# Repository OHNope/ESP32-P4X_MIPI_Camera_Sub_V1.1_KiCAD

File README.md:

# ESP32-P4-Function-EV-Board MIPI Camera Sub V1.1 — KiCad

[中文](#中文) | [English](#english)

---

## 中文

这是 Espressif 官方开发板 **ESP32-P4-Function-EV-Board** 的 MIPI 相机转接板（Camera Adapter Board, Camera Sub V1.1, 2024-05-29）的 KiCad 工程。设计版权归 Espressif 所有；本仓库只是把官方 OrCAD/Allegro 设计数据转成 KiCad，并修复了导入过程中出现的问题。

### 官方资料

- 开发板用户指南 (v1.5.2)：<https://docs.espressif.com/projects/esp-dev-kits/en/latest/esp32p4/esp32-p4-function-ev-board/user_guide.html>
- 相机转接板原理图 (PDF)：<https://dl.espressif.com/dl/schematics/esp32-p4-function-ev-board-camera-subboard-schematics.pdf>
- 相机转接板 PCB 布局 (PDF)：<https://dl.espressif.com/dl/schematics/esp32-p4-function-ev-board-camera-subboard-pcb-layout.pdf>
- 官方参考设计包（OrCAD DSN、Allegro BRD、Gerber、BOM、贴片文件）：<https://dl.espressif.com/schematics/CameraAdapterBoardReferenceDesign.zip>

### 为什么需要这个仓库

KiCad 的 OrCAD `.DSN` 导入功能目前只在 Nightly (10.99) 里有，正式版要等到 KiCad 11。即使能导入，解析结果和 Board Setup 的映射也有不少问题，导入后直接跑会有大量 ERC/DRC 报错。本工程逐项修正了这些导入问题，电路连接与官方设计保持一致。

### 打开方式

- **KiCad 10.0 及以上**即可打开（已在 KiCad 10.0.5 正式版和 Nightly 10.99 上验证）。转换和修复是在 Nightly 10.99 里完成的，之后用 KiCad 10.0.5 原生重存为 10.0 格式，以便正式版直接使用，KiCad 11 也能打开。降级前后的网表、焊盘/过孔坐标、坐标文件、Gerber 与钻孔几何、ERC/DRC 结果逐项比对一致。
- 用 KiCad 打开 `SCH_ESP32-P4_FUNCTION_EV_BOARD_MIPI_Camera_Sub_V1.1_20240529.kicad_pro`。
- 符号库 `orcad_import` 和封装库 `Camera_Sub` 都在工程目录内，已通过项目库表 (`sym-lib-table` / `fp-lib-table`) 注册，不依赖任何全局库。

### 检查结果（KiCad 10.0.5 与 Nightly 10.99 `kicad-cli`，结果相同）

| 检查 | 结果 |
| --- | --- |
| ERC | 0 |
| DRC 错误 | 0 |
| 未连接项 | 0 |
| 原理图 / PCB 一致性 | 0 |
| DRC 警告 | 57 条丝印警告，与官方 Gerber 一致（见下文） |

剩余 57 条丝印警告来自原设计本身，已对照官方 Gerber 确认，没有修改：位号字高 0.635 mm 低于 KiCad 默认下限 0.8 mm（33 条）；J1/SW1 的丝印跨过焊盘，生产时由阻焊裁掉（23 条）；"Same-Side FFC" 文字与 R20 丝印相碰（1 条）。

### 修复内容

原理图（OrCAD 导入）：
- 导入器把 OrCAD 的 "Power" 引脚全部映射为 `power_in`，导致 LDO（U1/U2）的 OUT 也成了电源输入，1V8/2V8 无驱动源。已改为 `power_out`。
- 符号库 `orcad_import` 未注册：导出为项目库 `orcad_import.kicad_sym`。
- `Footprint` 字段为空（封装名在 `OrCAD Footprint` 字段中）：已填写为 `Camera_Sub:<封装名>`。
- 3V3/GND 由 J1 从主板引入，添加 PWR_FLAG。
- 4 根 OrCAD 风格的带标签短线一端悬空：截短到标签位置，拓扑不变。
- 工程把原理图图框设为 `empty.kicad_wks`（只画 OrCAD 自带的图框和标题栏），但没有这个文件：KiCad 会退回默认图框，与 OrCAD 标题栏重叠，KiBot 打印原理图时直接报错。已补上空图框文件。

PCB（Allegro 导入）：
- 封装没有库名、Value 和原理图关联：从板上实物封装生成项目封装库 `Camera_Sub.pretty`，补全库名、Value、符号关联和原理图字段。
- 网络名与原理图不一致：标签网络加 `/` 前缀；`Net_xx` 单焊盘网络改为原理图的 `unconnected-(…)` 名称。已逐焊盘与原理图网表核对。
- 两个无位号的 Allegro 机械图形：命名为 MECH1/MECH2 并设为 board-only。
- 约束为 KiCad 默认值：恢复 Allegro 约束（最小线宽 0.127 mm、最小钻孔 0.25 mm）。
- 网络类按实际铜皮分配：`DP_CSI_A_*`（CSI 差分对，0.1778 mm）、`CS_0`（普通信号，0.127 mm）、`POWER`（3V3/AVDD_2V8/DOVDD_1V8/GND，0.635 mm，过孔 0.762/0.5）；预设线宽、过孔和差分对尺寸表填入板上实际使用的尺寸。
- GND 铺铜：间距 0.1778 mm、焊盘实心连接，重新填充。
- 封装的 courtyard 和 Fab 层只是焊盘外框：导入得到的 `Camera_Sub` 封装，F.CrtYd 基本就是焊盘的外接矩形（FFC_24P_0P5 的甚至比焊盘还小），SOT23-5 沿本体长边只有 2.4 mm，比 2.9 mm 的本体还短；F.Fab 要么没有，要么也只是焊盘框。这些形状来自 Espressif 原 Allegro 文件本身：KiCad 把 Allegro 的 place-bound（`PLACE_BOUND_TOP`）原样转成 F.CrtYd、装配外形（`ASSEMBLY_TOP`）转成 F.Fab，而原库的 place-bound 只框住焊盘、不含本体和余量（Allegro 靠封装间距规则控制间距，不靠这个框）。用 KiCad 10.0.5 重新导入官方 BRD，得到的 courtyard/Fab 与本工程首个提交逐个相同，所以不是导入器的问题。这样 KiCad 的 courtyard 重叠检查对这些封装几乎不起作用：在基于本工程的衍生设计里，两颗 SOT-23-5 本体贴在一起 DRC 也没有报错，直到 JLCPCB 贴片审核才发现。已按器件本体重画：F.Fab 画本体外形（IC 和晶振带 1 脚倒角），F.CrtYd 取焊盘和本体各外扩 0.15 mm 的并集，连接器、SOT 和 SW1 用多边形贴合。外扩 0.15 mm 时，两个 courtyard 相接对应 0.3 mm 的本体/焊盘间距，高于 JLCPCB 要求的 0.2 mm；Espressif 原布局仍然没有 courtyard 重叠。本体尺寸：0402 1.0×0.5、0603 1.6×0.8、SOT-23-5 2.9×1.6（ME6211、TI DBV）、SOT-363 2.0×1.25、3225 晶振 3.2×2.5、SW1 4.2×3.4（Espressif BOM）；J1/J2 用 JLCPCB 的 EasyEDA 元件外形（C262721、C2856805），J1 的外形比板边多出约 1.5 mm，与 JLCPCB 贴片预览一致。

### 版权与许可

设计版权归 Espressif Systems (Shanghai) Co., Ltd. 所有。本仓库**不授予任何许可**，详见 [LICENSE](LICENSE)。本仓库为非营利性的学习与参考分享，与 Espressif 无关联、未获其背书；如 Espressif 提出异议，将立即删除。

---

## English

KiCad project for the MIPI Camera Adapter Board (Camera Sub V1.1, 2024-05-29) of Espressif's **ESP32-P4-Function-EV-Board**. The design is copyright Espressif. This repository only converts Espressif's OrCAD/Allegro design data to KiCad and fixes the problems introduced by the import.

### Official resources

- Board user guide (v1.5.2): <https://docs.espressif.com/projects/esp-dev-kits/en/latest/esp32p4/esp32-p4-function-ev-board/user_guide.html>
- Camera adapter board schematic (PDF): <https://dl.espressif.com/dl/schematics/esp32-p4-function-ev-board-camera-subboard-schematics.pdf>
- Camera adapter board PCB layout (PDF): <https://dl.espressif.com/dl/schematics/esp32-p4-function-ev-board-camera-subboard-pcb-layout.pdf>
- Official reference design package (OrCAD DSN, Allegro BRD, Gerbers, BOM, placement): <https://dl.espressif.com/schematics/CameraAdapterBoardReferenceDesign.zip>

### Why

KiCad's OrCAD `.DSN` importer is currently only in the Nightly builds (10.99) and will ship in KiCad 11. Even then, the parser and the Board Setup mapping get a lot wrong, and a fresh import reports many ERC/DRC errors. This project fixes those import problems one by one. The connectivity matches the official design.

### Opening the project

- **Opens in KiCad 10.0 or later** (verified on KiCad 10.0.5 stable and Nightly 10.99). The conversion and fixes were done in Nightly 10.99, then the files were re-saved natively by KiCad 10.0.5 in the 10.0 format so the stable release can use them; KiCad 11 will open them too. Netlist, pad/via coordinates, placement file, Gerber and drill geometry and ERC/DRC results were compared before and after the downgrade and match.
- Open `SCH_ESP32-P4_FUNCTION_EV_BOARD_MIPI_Camera_Sub_V1.1_20240529.kicad_pro`.
- The `orcad_import` symbol library and the `Camera_Sub` footprint library live in the project folder and are registered in the project library tables. No global libraries are needed.

### Check results (KiCad 10.0.5 and Nightly 10.99 `kicad-cli`, identical)

| Check | Result |
| --- | --- |
| ERC | 0 |
| DRC errors | 0 |
| Unconnected items | 0 |
| Schematic / PCB parity | 0 |
| DRC warnings | 57 silkscreen warnings, same as Espressif's Gerbers (see below) |

The 57 remaining silkscreen warnings come from the original design and were checked against Espressif's Gerbers: 0.635 mm reference text, below KiCad's default 0.8 mm minimum (33); J1/SW1 silkscreen crossing pads, clipped by the solder mask at fabrication (23); the "Same-Side FFC" text touching R20's silkscreen (1).

### What was fixed

Schematic (OrCAD import):
- The importer maps every OrCAD "Power" pin to `power_in`, so the LDO (U1/U2) OUT pins became inputs and 1V8/2V8 had no driver. Changed to `power_out`.
- The `orcad_import` symbol library was not registered: exported to the project library `orcad_import.kicad_sym`.
- Empty `Footprint` fields (the package name was in `OrCAD Footprint`): set to `Camera_Sub:<package>`.
- PWR_FLAGs added on 3V3/GND, which enter from the main board through J1.
- Four OrCAD-style labelled stub wires had a dangling end: trimmed to the label, topology unchanged.
- The project sets the schematic drawing sheet to `empty.kicad_wks` (so only the OrCAD frame and title block are drawn), but the file was missing: KiCad fell back to its default sheet, drawn over the OrCAD title block, and KiBot stops when printing the schematic. Added the empty drawing sheet.

PCB (Allegro import):
- Footprints had no library ID, value or symbol link: generated the project footprint library `Camera_Sub.pretty` from the placed footprints and filled in the library IDs, values, symbol links and schematic fields.
- Net names did not match the schematic: label nets now carry the `/` prefix and single-pad `Net_xx` nets use the schematic's `unconnected-(…)` names. Checked pad by pad against the schematic netlist.
- Two unreferenced Allegro drawing symbols are named MECH1/MECH2 and set to board-only.
- Constraints were KiCad defaults: restored the Allegro values (0.127 mm minimum track, 0.25 mm minimum drill).
- Netclasses assigned from the routed copper: `DP_CSI_A_*` (CSI differential pairs, 0.1778 mm), `CS_0` (ordinary signals, 0.127 mm), `POWER` (3V3/AVDD_2V8/DOVDD_1V8/GND, 0.635 mm, 0.762/0.5 vias). The pre-defined track, via and differential-pair size tables hold the sizes used on the board.
- GND pour: 0.1778 mm clearance with solid pad connection, refilled.
- Footprint courtyards and Fab outlines only traced the pads: in the imported `Camera_Sub` footprints, F.CrtYd was essentially the pads' bounding box (smaller than the pads on FFC_24P_0P5), so SOT23-5's courtyard was 2.4 mm along the body, shorter than its 2.9 mm body; F.Fab was missing or also just the pad box. These shapes come from Espressif's Allegro file itself: KiCad converts Allegro place-bounds (`PLACE_BOUND_TOP`) to F.CrtYd and assembly outlines (`ASSEMBLY_TOP`) to F.Fab as they are, and the original library's place-bounds only enclose the pads, with no body and no margin (Allegro keeps parts apart with package-to-package spacing rules, not with this outline). A fresh import of the official BRD in KiCad 10.0.5 gives the same courtyards and Fab outlines as this repository's first commit, so the importer is not at fault. KiCad's courtyard-overlap check therefore hardly worked for these footprints: in a design derived from this project, two SOT-23-5 bodies touched without any DRC error, and JLCPCB's assembly review caught it. Redrawn from the component bodies: F.Fab is the body outline (with a pin-1 chamfer on the ICs and the crystal), and F.CrtYd is the union of the pads and the body, each grown by 0.15 mm, drawn as a polygon on the connectors, the SOT packages and SW1. With 0.15 mm, touching courtyards mean 0.3 mm between bodies or pads, above JLCPCB's 0.2 mm minimum, and Espressif's own placement still has no courtyard overlap. Body sizes: 0402 1.0×0.5, 0603 1.6×0.8, SOT-23-5 2.9×1.6 (ME6211, TI DBV), SOT-363 2.0×1.25, 3225 crystal 3.2×2.5, SW1 4.2×3.4 (Espressif BOM); J1/J2 use JLCPCB's EasyEDA component outlines (C262721, C2856805). J1's outline reaches about 1.5 mm past the board edge, as in JLCPCB's assembly preview.

### Copyright and license

The design is copyright Espressif Systems (Shanghai) Co., Ltd. This repository **grants no license**; see [LICENSE](LICENSE). It is a non-commercial share for study and reference, is not affiliated with or endorsed by Espressif, and will be taken down if Espressif objects.

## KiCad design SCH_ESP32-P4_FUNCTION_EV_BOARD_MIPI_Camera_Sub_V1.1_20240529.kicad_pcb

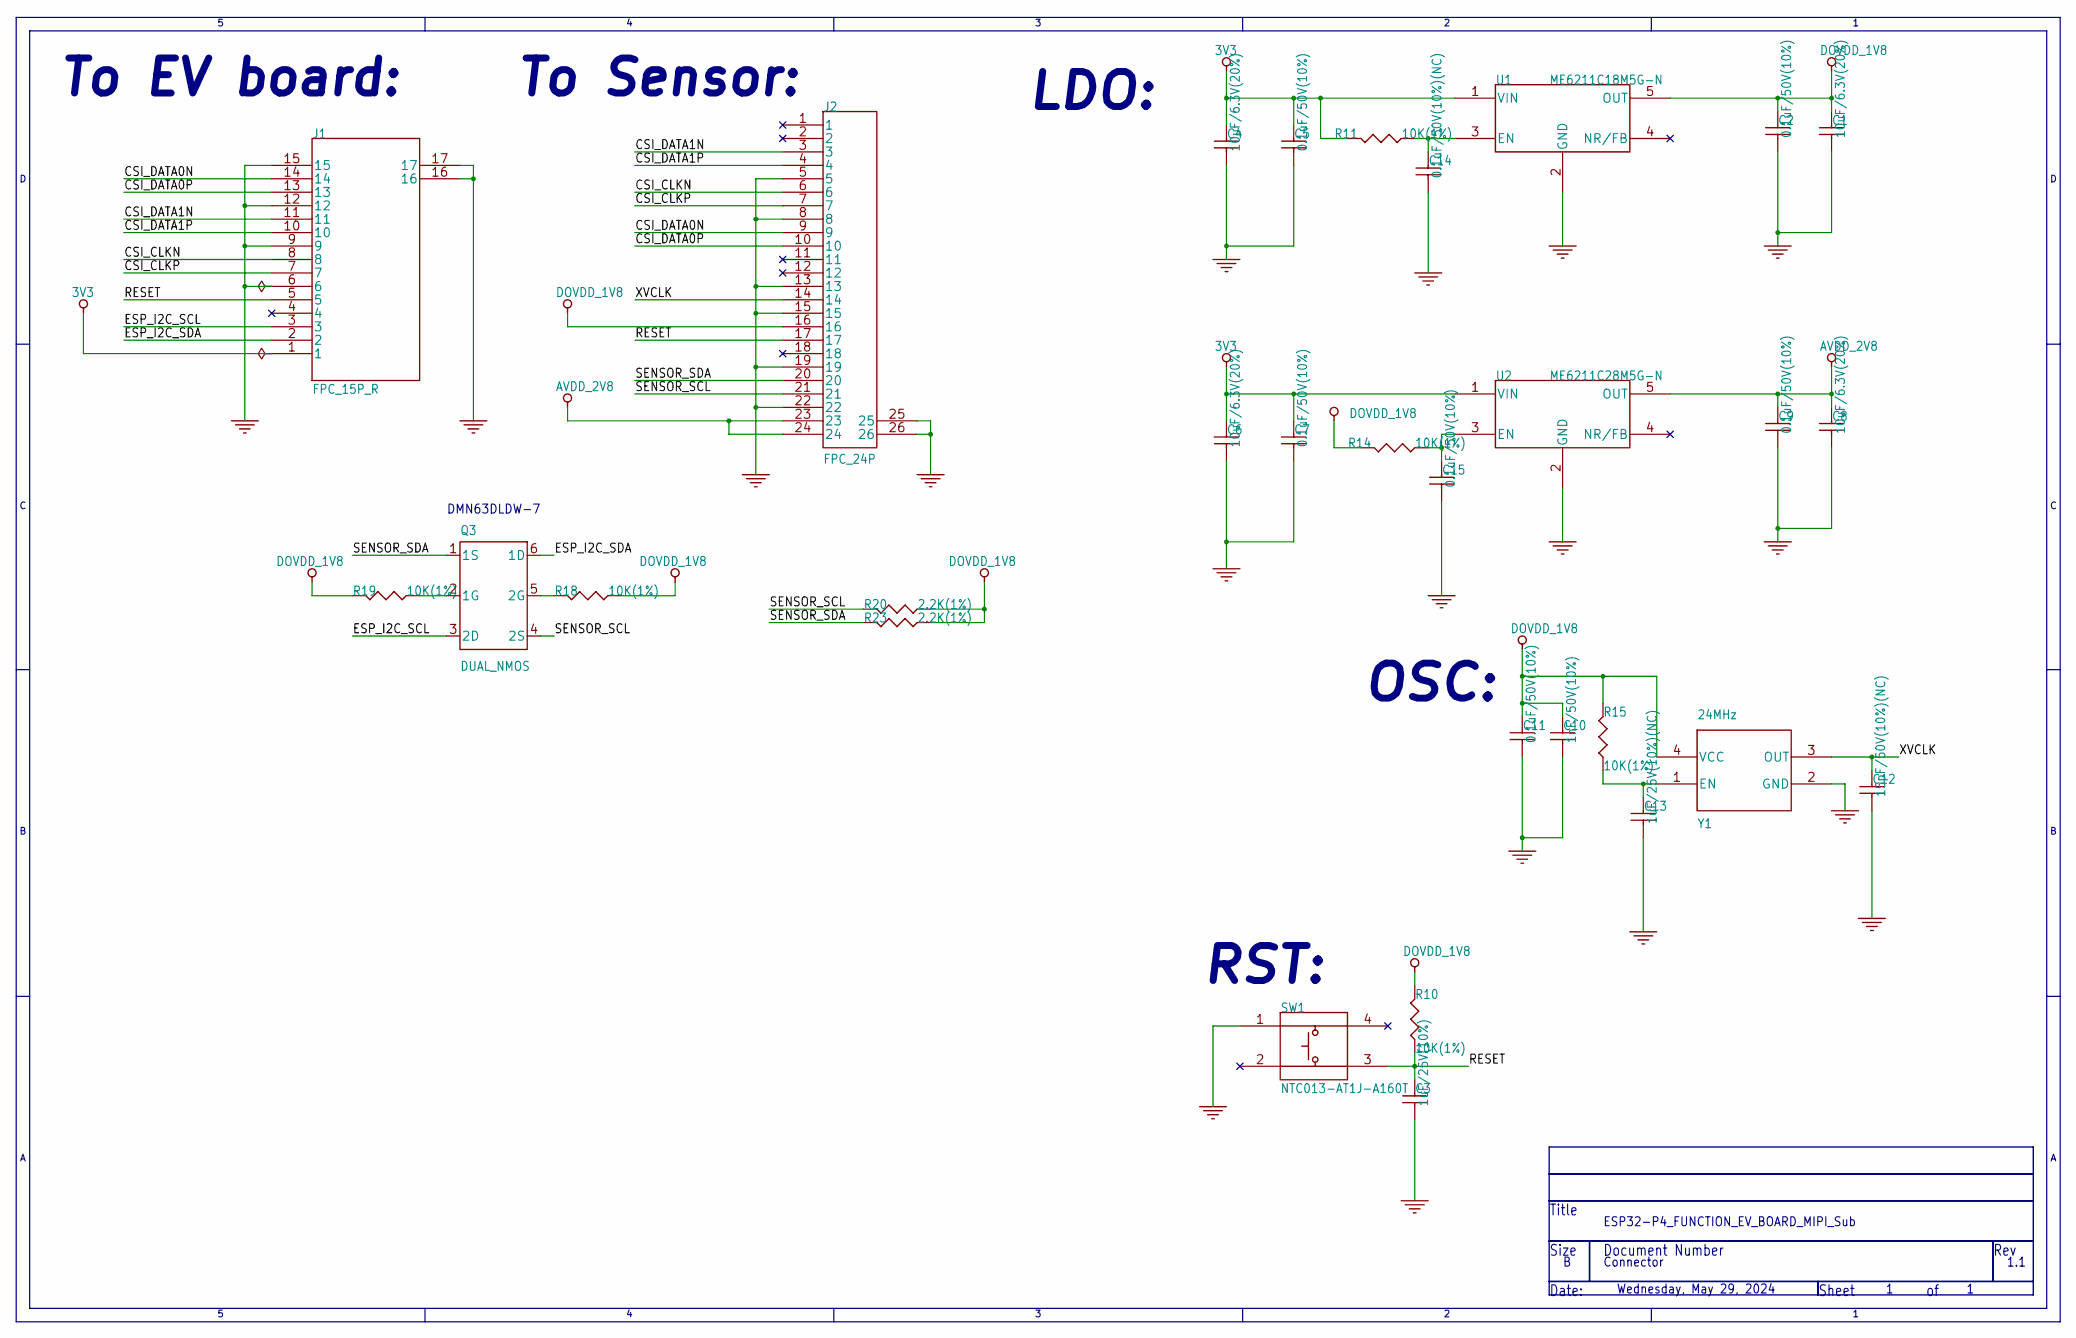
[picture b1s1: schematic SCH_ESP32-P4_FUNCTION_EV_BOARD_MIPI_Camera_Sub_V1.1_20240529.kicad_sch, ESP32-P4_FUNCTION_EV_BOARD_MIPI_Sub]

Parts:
C1, C4, C6, C8: 10uF/6.3V(20%); C0603
C2, C5, C7, C9, C11, C15: 0.1uF/50V(10%); C0402; Part Number ES110451066200
C3: 1uF/25V(10%); C0402; Part Number ES110451066200
C10: 1nF/50V(10%); C0402; Part Number ES110451066200
C12: 15pF/50V(10%)(NC); C0402; Part Number ES110451066200
C13: 1uF/25V(10%)(NC); C0402; Part Number ES110451066200
C14: 0.1uF/50V(10%)(NC); C0402; Part Number ES110451066200
J1: FPC_15P_R; FFC_15P_1_MIPI_R
J2: FPC_24P; FFC_24P_0P5
Q3: DUAL_NMOS; SOT-363
R10, R11, R14, R15, R18, R19: 10K(1%); R0402; Part Number ES210400000000
R20, R23: 2.2K(1%); R0402; Part Number ES210400000000
SW1: NTC013-AT1J-A160T; SW4-4P2X3P2X2P5-SMT; Part Number ES511600400000
U1: ME6211C18M5G-N; SOT23-5; Part Number ES41140207000000
U2: ME6211C28M5G-N; SOT23-5; Part Number ES41140207000000
Y1: 24MHz; XTAL3225

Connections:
3V3: C4.1, C5.1, C6.1, C7.1, J1.1, R11.2, U1.1 (VIN), U2.1 (VIN)
/CSI_CLKN: J1.8, J2.6
/CSI_CLKP: J1.7, J2.7
/CSI_DATA0N: J1.14, J2.9
/CSI_DATA0P: J1.13, J2.10
/CSI_DATA1N: J1.11, J2.3
/CSI_DATA1P: J1.10, J2.4
/ESP_I2C_SCL: J1.3, Q3.3 (2D)
/ESP_I2C_SDA: J1.2, Q3.6 (1D)
/RESET: C3.1, J1.5, J2.17, R10.1, SW1.3
/SENSOR_SCL: J2.21, Q3.4 (2S), R20.2
/SENSOR_SDA: J2.20, Q3.1 (1S), R23.2
/XVCLK: C12.1, J2.14, Y1.3 (OUT)
AVDD_2V8: C8.1, C9.1, J2.23, J2.24, U2.5 (OUT)
DOVDD_1V8: C1.1, C2.1, C10.1, C11.1, J2.16, R10.2, R14.2, R15.2, R18.1, R19.2, R20.1, R23.1, U1.5 (OUT), Y1.4 (VCC)
GND: C1.2, C2.2, C3.2, C4.2, C5.2, C6.2, C7.2, C8.2, C9.2, C10.2, C11.2, C12.2, C13.2, C14.2, C15.2, J1.6, J1.9, J1.12, J1.15, J1.16, J1.17, J2.5, J2.8, J2.13, J2.15, J2.19, J2.22, J2.25, J2.26, SW1.1, U1.2 (GND), U2.2 (GND), Y1.2 (GND)
unnamed: Q3.2 (1G), R19.1
unnamed: Q3.5 (2G), R18.2
unnamed: C14.1, R11.1, U1.3 (EN)
unnamed: C15.1, R14.1, U2.3 (EN)
unnamed: C13.1, R15.1, Y1.1 (EN)

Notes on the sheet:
OSC:
Size
DMN63DLDW-7
Connector
1.1
RST:
Document Number
Wednesday, May 29, 2024
Rev
LDO:
Sheet
ESP32-P4_FUNCTION_EV_BOARD_MIPI_Sub
Title
To EV board:
Date:
To Sensor:

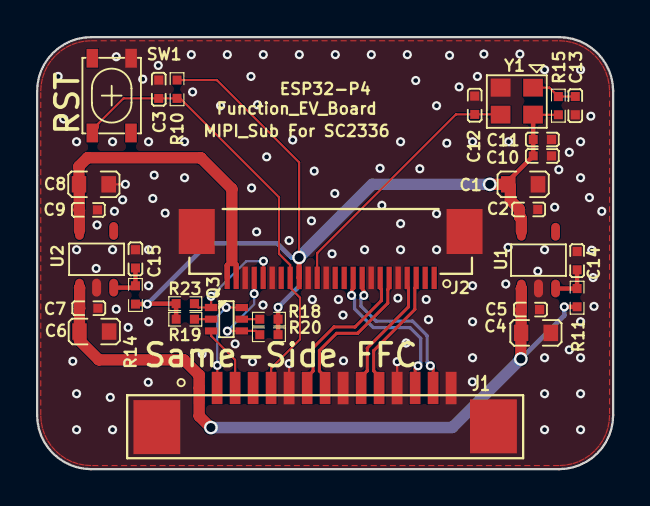
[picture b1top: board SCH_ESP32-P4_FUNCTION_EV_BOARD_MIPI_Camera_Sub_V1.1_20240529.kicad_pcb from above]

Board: 4 copper layers, 32.0 x 24.0 mm, 32 parts (0 on the bottom side), 21 nets.

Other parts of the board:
MECH1, MECH2: (no value)

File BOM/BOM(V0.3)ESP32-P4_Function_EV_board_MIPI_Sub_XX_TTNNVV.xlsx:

BOM(V0.3)_ESP32-P4_Function_EV_board_MIPI_Sub_XX_TTNNVV
Item Number | Quantity | Part Reference | Value | PCB Footprint | Description | Manufacturer | Manufacturer Part # | 备注
1 | 4 | C1,C4,C6,C8 | 10uF/6.3V(20%) | C0603 | MLCC
2 | 6 | C2,C5,C7,C9,C11,C15 | 0.1uF/50V(10%) | C0402 | MLCC
3 | 1 | C3 | 1uF/25V(10%) | C0402 | MLCC
4 | 1 | C10 | 1nF/50V(10%) | C0402 | MLCC
8 | 1 | J1 | FPC_15P_R | FFC_15P_1_MIPI_R | FFC连接器，间距1mm，15P，抽屉式下接 | 钜硕电子 | AFA07-S15FCA-00 | 参考：嘉立创C262721
9 | 1 | J2 | FPC_24P | FFC_24P_0P5 | FFC连接器，间距0.5mm，24P，翻盖式下接 | 讯普 | FPC-05F-24PH20 | 参考：嘉立创C2856805
10 | 1 | Q3 | DUAL_NMOS | SOT-363 | 双NMOS，耐压30V，电流220mA，阈值电压MAX1.5V | DIODES | DMN63D8LDW-7 | 注意阈值电压最大值小于1.8V
 |  |  |  |  |  | LRC | LBSS138DW1T1G
11 | 6 | R10,R11,R14,R15,R18,R19 | 10K(1%) | R0402 | Resistor
12 | 2 | R20,R23 | 2.2K(1%) | R0402 | Resistor
13 | 1 | SW1 | NTC013-AT1J-A160T | SW4-4P2X3P2X2P5-SMT | 4.2*3.4*2.5mm立贴,轻触开关 | 怡远 | YTS-A016-2 | 参考：嘉立创C2910673
14 | 1 | U1 | ME6211C18M5G-N | SOT23-5 | LDO | 微盟 | ME6211C18M5G-N | 参考：嘉立创C236671
15 | 1 | U2 | ME6211C28M5G-N | SOT23-5 | LDO | 微盟 | ME6211C28M5G-N | 参考：嘉立创C53099
16 | 1 | Y1 | 24MHz | XTAL3225 | 24MHz有源晶振 1.8V-3.3V ±10ppm | MDH | 2.1.3.2400037
17 | 1 | - | - | - | ESP32-P4_FUNCTION_EV_BOARD_MIPI_Sub_V1.1, 4L, 32.0*24.0*1.6mm, 哑光黑色阻焊, 白色字符, 无铅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 | - | - | -
